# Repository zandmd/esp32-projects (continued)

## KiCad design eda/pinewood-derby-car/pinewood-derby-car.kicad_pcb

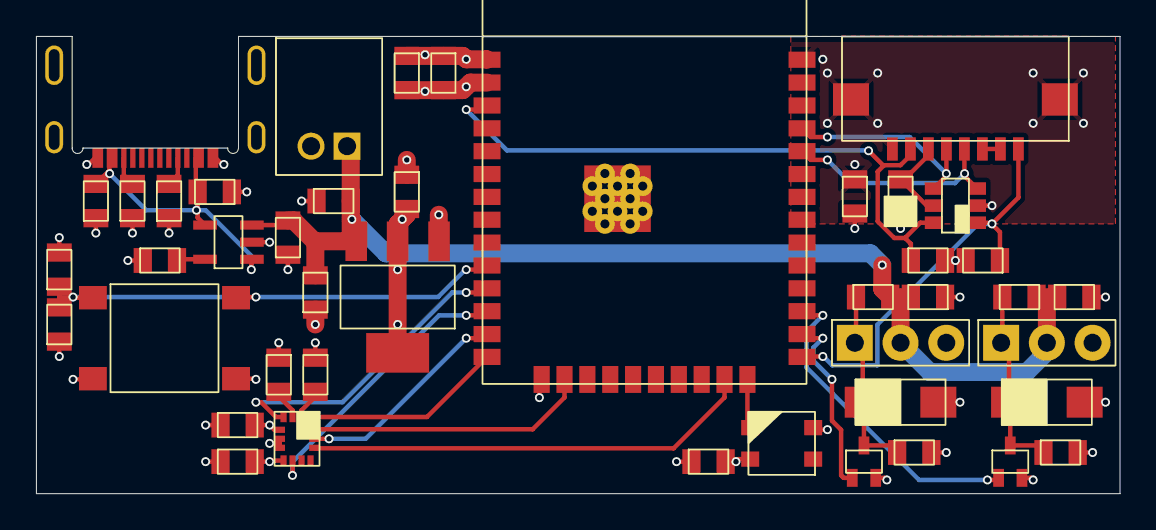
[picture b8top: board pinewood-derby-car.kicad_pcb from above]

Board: 4 copper layers, 60.2 x 25.4 mm, 44 parts (0 on the bottom side), 27 nets.

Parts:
C1, C4: 22 uF; PASSIVE-NPOL-0805
C2, C12, C13, C14, C15: 0.1 uF; PASSIVE-NPOL-0805
C3, C5, C6, C7, C8, C10, C11: 1 uF; PASSIVE-NPOL-0805
C9: 10 uF; PASSIVE-NPOL-0805
D1: PASSIVE-POL-0805
D2: CM1293A-04SO
D3, D4: SMAJ5.0A
J1: USB4520-03-0-A
J2: CF25081D0R0-10-NH
J3: S2B-PH-K-S
J4, J5: PH1-03-UA
Q1, Q2: BSS816NWH6327XTSA1
R1, R2: 5.1k; PASSIVE-NPOL-0805
R3: 2.7k; PASSIVE-NPOL-0805
R4, R5, R6, R7, R8, R9, R10, R11, R12: 10k; PASSIVE-NPOL-0805
S1: PTS645SM43SMTR92 LFS
U1: ESP32-WROOM-32E-N4
U2: MCP73812T-420I/OT; MCP73812T-420IOT
U3: AZ1117IH-3.3TRG1
U4: LSM6DSOTR
U5: 2659

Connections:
+3V3: C1.2, C2.2, C4.2, C5.2, C13.2, C14.2, C15.2, D1.1, R4.2, R5.2, R6.2, R11.2, R12.2, U1.2 (3V3), U3.2 (OUTPUT), U4.5 (VDDIO), U4.8 (VDD), U5.4 (VDD)
+5V: C3.2, C6.2, J1.A4 (VBUS), J1.A9 (VBUS), J1.B4 (VBUS), J1.B9 (VBUS), U2.1 (CE), U2.4 (VDD)
/Channel 0/IN: Q1.1 (G), U1.26 (GPO4)
/Channel 1/IN: Q2.1 (G), U1.27 (GPO16)
/Microcontroller/BTN: C12.2, R6.1, S1.1, S1.2, U1.10 (GPI25)
/Microcontroller/CS: U1.23 (HSPIM.CS(PULL_UP+PWM)), U4.12 (CS)
/Microcontroller/EN: D2.6 (CH4), J2.7 (S:EN), R4.1, U1.3 (EN)
/Microcontroller/INT1: U1.11 (GPI26), U4.4 (INT1)
/Microcontroller/INT2: U1.12 (GPI27), U4.9 (INT2)
/Microcontroller/IO0: D2.1 (CH1), J2.1 (S:IO0), R5.1, U1.25 (GPI0(PULL_DOWN))
/Microcontroller/LED: U1.24 (GPO2(PULL_DOWN)), U5.3 (DIN)
/Microcontroller/MISO: U1.14 (HSPIM.MISO(PULL_DOWN)), U4.1 (MISO)
/Microcontroller/MOSI: U1.16 (HSPIM.MOSI), U4.14 (MOSI)
/Microcontroller/RXD: D2.3 (CH2), J2.4 (S:RXD), U1.34 (U0RXD(PWM))
/Microcontroller/SCLK: U1.13 (HSPIM.SCLK(PWM)), U4.13 (SCL)
/Microcontroller/TXD: D2.4 (CH3), J2.5 (S:TXD), U1.35 (U0TXD(PWM))
GND: C1.1, C2.1, C3.1, C4.1, C5.1, C6.1, C7.1, C8.1, C9.1, C10.1, C11.1, C12.1, C13.1, C14.1, C15.1, D2.2 (VN), D3.2, D4.2, J1.A1 (GND), J1.A12 (GND), J1.B1 (GND), J1.B12 (GND), J1.SHELL (GND), J2.8 (S:GND), J2.9 (GND), J3.2 (-), J4.3 (-), J5.3 (-), Q1.2 (S), Q2.2 (S), R1.1, R2.1, R3.1, R9.1, R10.1, S1.3, S1.4, U1.1 (GND), U1.15 (GND), U1.38 (GND), U1.39 (GND), U2.2 (VSS), U3.1 (GND), U4.6 (GND), U4.7 (GND), U5.2 (VSS)
unnamed: D1.2, D2.5 (VP), J2.6 (S:3V3)
unnamed: J1.A5 (CC1), R2.2
unnamed: J1.B5 (CC2), R1.2
unnamed: J2.2 (S:5V_IN), J2.3 (S:5V_OUT)
unnamed: D3.1, J4.1 (S), Q1.3 (D), R7.1, R11.1
unnamed: D4.1, J5.1 (S), Q2.3 (D), R8.1, R12.1
unnamed: R3.2, U2.5 (PROG)
unnamed: R9.2, U4.3 (SCx)
unnamed: R10.2, U4.2 (SDx)
VBAT: C7.2, C8.2, C9.2, C10.2, C11.2, J3.1 (+), J4.2 (+), J5.2 (+), R7.2, R8.2, U2.3 (VBAT), U3.3 (INPUT)

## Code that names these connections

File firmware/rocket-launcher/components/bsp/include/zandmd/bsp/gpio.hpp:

#ifndef ZANDMD_BSP_GPIO_HPP
#define ZANDMD_BSP_GPIO_HPP

#include <zandmd/peripheral-alloc/gpio_map.hpp>

ZANDMD_GPIO(btn_c0, 34);
ZANDMD_GPIO(btn_c1, 35);
ZANDMD_GPIO(btn_r0, 21);
ZANDMD_GPIO(btn_r1, 32);
ZANDMD_GPIO(btn_r2, 33);
ZANDMD_GPIO(cs, 5);
ZANDMD_GPIO(fire0, 26);
ZANDMD_GPIO(fire1, 27);
ZANDMD_GPIO(fire2, 16);
ZANDMD_GPIO(fire3, 17);
ZANDMD_GPIO(led, 14);
ZANDMD_GPIO(miso, 19);
ZANDMD_GPIO(mosi, 23);
ZANDMD_GPIO(rfm_irq, 15);
ZANDMD_GPIO(rfm_rst,  22);
ZANDMD_GPIO(sclk, 18);
ZANDMD_GPIO(sense0, 25);
ZANDMD_GPIO(sense1, 12);
ZANDMD_GPIO(sense2, 2);
ZANDMD_GPIO(sense3, 4);
ZANDMD_GPIO(vbat, 13);

#include <zandmd/peripheral-alloc/gpio_map.hpp>

#endif

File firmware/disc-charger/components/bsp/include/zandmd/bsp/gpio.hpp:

#ifndef ZANDMD_BSP_GPIO_HPP
#define ZANDMD_BSP_GPIO_HPP

#include <zandmd/peripheral-alloc/gpio_map.hpp>

ZANDMD_GPIO(io0, 0);
ZANDMD_GPIO(txd, 1);
ZANDMD_GPIO(int2, 2);
ZANDMD_GPIO(rxd, 3);
ZANDMD_GPIO(adc_5v, 4);
ZANDMD_GPIO(miso, 12);
ZANDMD_GPIO(mosi, 13);
ZANDMD_GPIO(sclk, 14);
ZANDMD_GPIO(cs, 15);
ZANDMD_GPIO(neopixel, 16);
ZANDMD_GPIO(int1, 17);
ZANDMD_GPIO(led_dim, 25);
ZANDMD_GPIO(adc_bat, 32);
ZANDMD_GPIO(led_ctrl, 33);
ZANDMD_GPIO(btn, 36);

#include <zandmd/peripheral-alloc/gpio_map.hpp>

#endif

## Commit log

2023-10-10 Added EDA files
2023-10-10 Created first firmware project
2023-10-12 Added WS2811 driver
2023-10-12 Added button driver
2023-10-13 Added gesture support to button driver
2023-10-16 Added SPI driver
2023-10-16 Added power_dump driver
2023-10-16 Added IMU driver
2023-11-04 made folder structure
2023-11-04 made folders
2023-11-04 enable RGB LED x1
2023-11-04 LEDs doing the disco
2023-11-04 working buttons
2023-11-07 working LEDs with buttons:
2023-11-09 Added pinewood derby car app code
2023-11-09 Fixed build issue after refactored merge
2023-11-09 Updated rocket-launcher project for new format
2023-11-09 Added LoRa module driver
2023-11-09 Removed unused API
2023-11-10 Implemented charges
2023-11-10 Added battery driver
2023-11-10 Wrote untested application code
2023-11-11 Fixed startup crashes
2023-11-11 Fixed flickering LEDs
2023-11-11 Fixed crash after connecting charge
2023-11-11 Fixed log statements
2023-11-11 Fixed LoRa transmission rate
2023-11-11 Added radio link debugging log statements
2023-11-11 Added extra protection against fire button bounces
2023-11-11 Added warning logs for corrupt packets
2023-11-11 Added semaphores
2023-11-11 Added more ADC failure handling
2023-11-11 Added watchdog timer
2023-11-11 Fixed various state machine issues
2023-11-11 Added test plan
2023-11-11 Fixed needing to reset radio after some weird boot conditions
2023-12-09 Updated charge firing time
2023-12-09 Created neopixel-controller firmware project
2023-12-09 Implemented neopixel-controller/hwtest
2023-12-12 Updated for lights on house
2023-12-13 Improved LED graphics framework
2023-12-14 Made c_cpp_properties.json auto-generate
2023-12-14 Added Wi-Fi support
2023-12-14 Added workaround to disable Wi-Fi
2023-12-14 Fixed stripe() direction
2023-12-16 Made the direction reverse occasionally
2023-12-16 Updated to a static pattern
2023-12-17 Switched lights to purple/white
2023-12-17 Created disc-charger firmware project
2023-12-18 Allowed color_wipe() to start from the center of a span
2023-12-19 Updated pattern yet again
2023-12-19 Fixed gpio_isr_service with pin numbers >= 32
2023-12-19 Added button to disc-charger/hwtest
2023-12-19 Added neopixel to disc-charger/hwtest
2023-12-19 Added basic IMU driver to disc-charger/hwtest
2023-12-19 Added ADC driver to disc-charger/hwtest
2023-12-19 Added UV LEDs to disc-charger/hwtest
2023-12-20 Updated to a random pattern
2023-12-21 Added rainbow mode
2023-12-23 Wrote disc charger app code
2023-12-23 Added symmetric partial rainbow pattern
2023-12-27 Fixed building with other versions of Python
